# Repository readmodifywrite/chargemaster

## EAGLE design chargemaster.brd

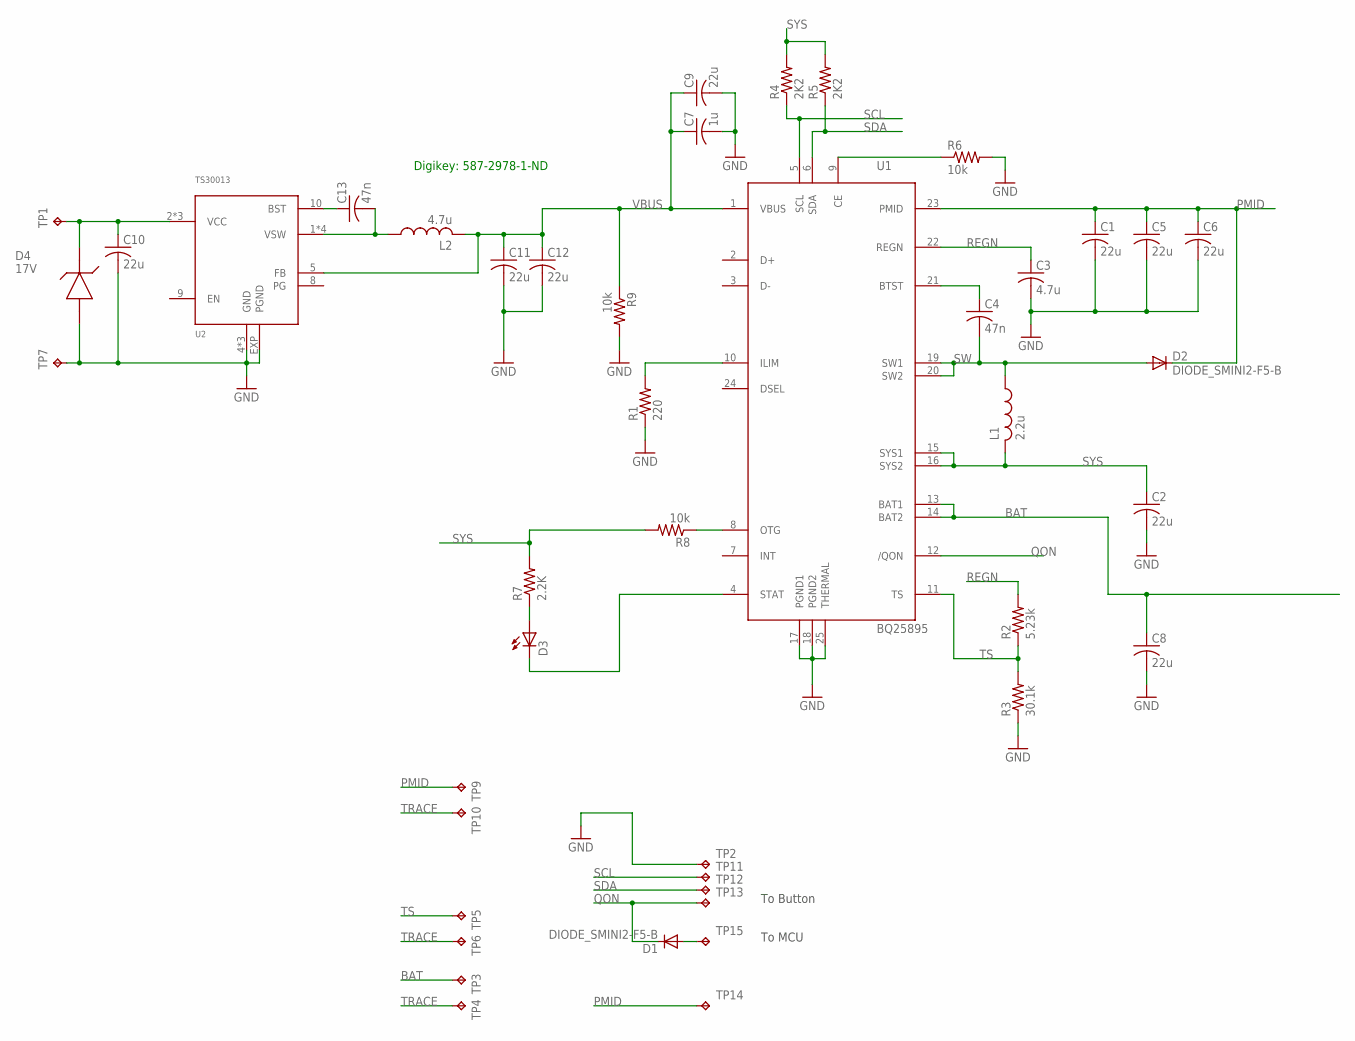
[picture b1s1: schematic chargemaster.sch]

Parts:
C1, C2, C5, C6, C8, C9, C10, C11, C12: 22u; C1206
C3: 4.7u; C0805
C4, C13: 47n; C0402
C7: 1u; C0603
D1, D2: DIODE_SMINI2-F5-B; SMINI2-F5-B
D3: LEDCHIP-LED0805; CHIP-LED0805
D4: 17V; SMA
L1: 2.2u; SRN8040TA
L2: 4.7u; SRN8040TA
R1: 220; R0603
R2: 5.23k; R0603
R3: 30.1k; R0603
R4, R5: 2K2; R0603
R6, R8, R9: 10k; R0603
R7: 2.2K; R0603
TP1, TP2, TP3, TP4, TP5, TP6, TP7, TP9, TP10, TP11, TP12, TP13, TP14, TP15: TPPAD1-13Y; P1-13Y
U1: BQ25895; QFN24_4X4
U2: TS30013; QFN16_3X3

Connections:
BAT: C8.1, TP3.TP, U1.13 (BAT1), U1.14 (BAT2)
BST: C13.1, U2.10 (BST)
BTST: C4.1, U1.21 (BTST)
unnamed: D3.A, R7.1
unnamed: D3.C, U1.4 (STAT)
unnamed: R1.2, U1.10 (ILIM)
unnamed: D1.P$1 (A), TP15.TP
unnamed: R6.1, U1.9 (CE)
unnamed: R8.1, U1.8 (OTG)
PMID: C1.1, C5.1, C6.1, D2.P$2 (C), TP9.TP, TP14.TP, U1.23 (PMID)
QON: D1.P$2 (C), TP13.TP, U1.12 (/QON)
REGN: C3.1, R2.2, U1.22 (REGN)
SCL: R4.1, TP11.TP, U1.5 (SCL)
SDA: R5.1, TP12.TP, U1.6 (SDA)
SW: C4.2, D2.P$1 (A), L1.P$1 (1), U1.19 (SW1), U1.20 (SW2)
SYS: C2.1, L1.P$2 (2), R4.2, R5.2, R7.2, R8.2, U1.15 (SYS1), U1.16 (SYS2)
TRACE: C1.2, C2.2, C3.2, C5.2, C6.2, C7.2, C8.2, C9.2, C10.2, C11.2, C12.2, D4.P$2 (GND), R1.1, R3.1, R6.2, R9.2, TP2.TP, TP4.TP, TP6.TP, TP7.TP, TP10.TP, U1.17 (PGND1), U1.18 (PGND2), U1.25 (THERMAL), U2.4 (GND), U2.14 (GND), U2.15 (GND), U2.EXP (PGND)
TS: R2.1, R3.2, TP5.TP, U1.11 (TS)
VBUS: C7.1, C9.1, C11.1, C12.1, L2.P$2 (2), R9.1, U1.1 (VBUS), U2.5 (FB)
VIN: C10.1, D4.P$1 (LINE), TP1.TP, U2.2 (VCC), U2.3 (VCC), U2.11 (VCC)
VSW: C13.2, L2.P$1 (1), U2.1 (VSW), U2.12 (VSW), U2.13 (VSW), U2.16 (VSW)

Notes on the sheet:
To MCU
To Button
Digikey: 587-2978-1-ND

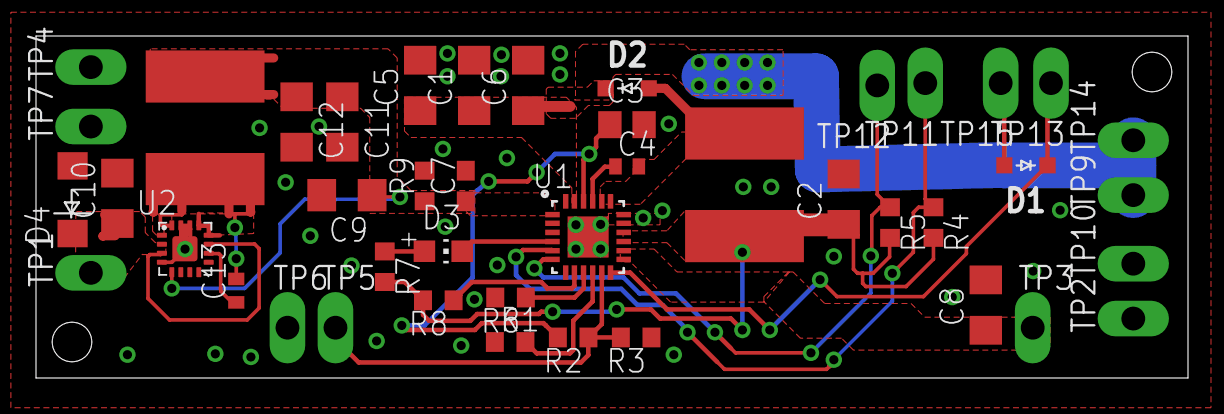
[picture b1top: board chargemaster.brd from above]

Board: 2 copper layers, 64.0 x 19.0 mm, 44 parts (0 on the bottom side), 21 nets.
